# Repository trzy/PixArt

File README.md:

# PixArt PAJ7025R2 6dof Tracking Demo with Arduino and Windows

*Copyright 2017-2019 Bart Trzynadlowski*

## Overview

The PixArt PAJ7025R2 is an infrared camera with integrated DSP capable of tracking multiple IR light sources at high frame rates. Its predecessor was used in Nintendo's Wii Remote controller. [Johnny Chung Lee](http://johnnylee.net/projects/wii/), [Oliver Kreylos](https://web.cs.ucdavis.edu/~okreylos/ResDev/Wiimote/index.html  ), and [Franklin Ta](https://franklinta.com/2014/09/30/6dof-positional-tracking-with-the-wiimote/) have each demonstrated how to use the Wii sensor
for fun 6dof tracking applications.

In 2017, I got the idea to use the sensor in conjunction with Microsoft HoloLens for 6dof tracking of a tennis racket. I only got as far as
fabricating a test PCB to mount the chip before I shelved it. Two years later, feeling bad that I had never done anything with the boards, I built a PC
interface using Arduino and wrote a simple program to track and render an IR target in real-time.

This repository includes:

- Arduino code for the [Adafruit Feather nRF52 Bluefruit LE (nRF52832) board](https://www.adafruit.com/product/3406)
- Windows code for pose estimation (OpenCV 4.0.1) and visualization (SDL2 and OpenGL)
- PCB schematics and Gerbers files sent to [PCB Unlimited](https://pcbunlimited.com/) for fabrication
- Photographs of the assembled hardware, including a simple 9V battery-powered target with four 875 nm IR LEDs ([TSHA4400](https://www.vishay.com/ir-emitting-diodes/list/product-81017/)) by Vishay Semiconductors.

The Arduino reads out the detection report for each frame and sends it to the Windows program, which runs OpenCV's perspective-n-point (PnP) solver to estimate the 6dof pose of a target with known dimensions.

A PAJ7025R3 part with a wider field of view exists. To my knowledge, it is the exact same IC but with a different lens, meaning a simple modification of the camera
intrinsics in `code/win32/src/include/pixart/camera_parameters.hpp` would be the only change needed to support it.

## Build Instructions

### Arduino

The Arduino code is located in `code/arduino/pa_driver`. The other Arduino programs are simple tests. [Follow the instructions from Adafruit](https://learn.adafruit.com/bluefruit-nrf52-feather-learning-guide/arduino-bsp-setup) for
installing the BSP and loading the code onto the board.

Connections between the PixArt PCB and the Arduino board are listed in the table below.

| PixArt PCB | nRF52832 |
| ---------- | -------- |
| J1 (VDDMA) | +3.3v (recommend pin nearest GND) |
| J2 (G9/CSB) | A0 |
| J3 (G10/SCK) | SCK |
| J4 (G11/MISO) | MISO |
| J5 (G12/MOSI) | MOSI |
| J6 (GND) | GND |

### Windows

The Windows program located in `code/win32` depends on:

- [Boost](https://www.boost.org/) 1.69.0
- [OpenCV](https://opencv.org) 4.0.1
- [SDL2](https://libsdl.org)

Newer versions of Boost and OpenCV are untested but should work.

A Makefile for GCC on Windows is included. Edit the *Search Paths* section as needed. I used [MSYS2](https://msys2.org) to install GCC and SDL2 via pacman. OpenCV and Boost were installed manually.
Once ready simply run Make from the `code/win32` directory in an MSYS2 shell or Windows Command Prompt:

```
make
```

Visual Studio users will unfortunately have to manually create a project. I will happily accept a pull request for Visual Studio or CMake.

## Usage

In `code/win32` run:

```
bin/object_visualizer.exe
```

Two windows will appear (probably atop each other), one showing the raw objects detected by the sensor and the other showing a visualization of
a ping pong paddle in 3D. This assumes that an identical IR target to mine is being used. The target is defined in `code/win32/src/apps/object_visualizer/perspective_window.cpp`.
If there is an error opening the COM port, make sure the USB drivers were installed. These should come bundled with the Arduino IDE but can also
be obtained directly ([instructions here](https://learn.adafruit.com/bluefruit-nrf52-feather-learning-guide/arduino-board-setup)).

To test without any hardware, some recorded data is provided in `code/win32/recordings`. For example, try:

```
bin/object_visualizer.exe --replay-from=recordings/paddle0.bin
```

To learn about command line options, run:

```
bin/object_visualizer.exe --help
```

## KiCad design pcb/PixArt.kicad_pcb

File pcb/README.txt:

Cutout
------

Cutout was created using an NPTH pad, with hole and pad dimensions being identical.  Then, the following procedure
was used to copy this to the Edge.Cuts layer (while also retaining it in "All copper layers", or wherever the hole appears
by default).

https://stackoverflow.com/questions/43949808/create-a-footprint-for-mounting-through-the-board-cut-in-kicad

  (pad "" np_thru_hole oval (at 0 0) (size 12.5 1.2) (drill oval 12.5 1.2) (layers *.Cu Eco1.User))
  (pad "" np_thru_hole oval (at 0 0) (size 12.5 1.2) (drill oval 12.5 1.2) (layers *.Cu Edge.Cuts))

Mounting Holes
--------------

Two mounting holes were created as NPTH pads with diameter 0.9 mm.

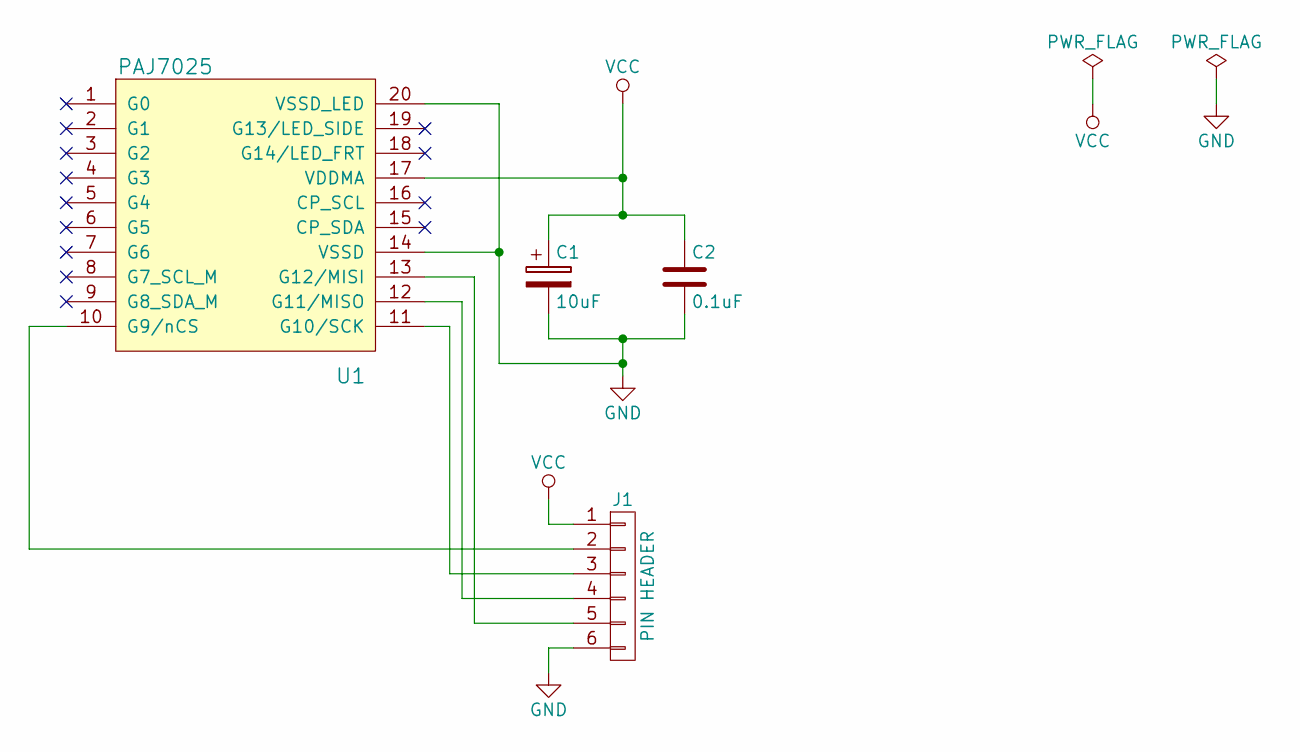
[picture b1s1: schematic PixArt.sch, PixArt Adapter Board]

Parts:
C1: 10uF; CP_Radial_D10.0mm_P2.50mm
C2: 0.1uF; C_Disc_D3.8mm_W2.6mm_P2.50mm
J1: PIN HEADER; Molex_KK-6410-06_06x2.54mm_Straight
U1: PAJ7025

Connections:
GND: C1.2, C2.2, J1.6, U1.14 (VSSD), U1.20 (VSSD_LED)
unnamed: J1.2, U1.10 (G9/nCS)
unnamed: J1.3, U1.11 (G10/SCK)
unnamed: J1.4, U1.12 (G11/MISO)
unnamed: J1.5, U1.13 (G12/MISI)
VCC: C1.1, C2.1, J1.1, U1.17 (VDDMA)

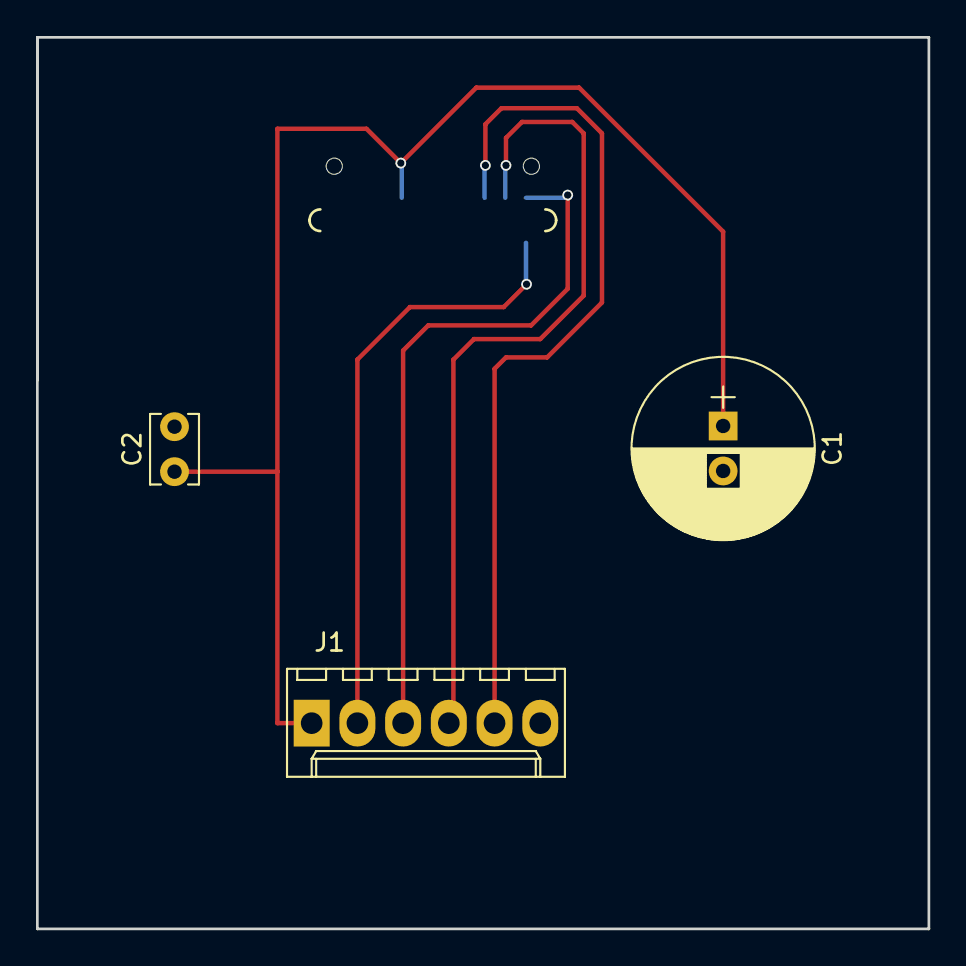
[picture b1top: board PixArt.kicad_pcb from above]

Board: 2 copper layers, 49.5 x 49.5 mm, 4 parts (0 on the bottom side), 6 nets.

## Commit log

2021-09-11 Report position every second
2021-09-11 Added IR LED datasheets and Feather board manuals
2021-09-11 Added TSHA4400 (875nm IR LED) datasheet. This LED confirmed to work with PixArt sensor.
2021-09-11 Whitespace
2021-09-11 Arduino pa_driver app can respond to peek and poke requests
2021-09-11 Added wait_for_packets(), which blocks until n expected packets are received
2021-09-11 Cooperative task object for periodic tasks
2021-09-11 Packet id member type is now PacketID
2021-09-11 USB ping test
2021-09-11 New packet_reader class for cooperatively reading packets from serial port stream
2021-09-11 Moved cooperative_task into util namespace, commented namespace closing brackets, whitespace fixes
2021-09-11 PixArt driver: set up and read object data, verify by printing to serial console
2021-09-11 Reorganized source code and added a Windows-based serial test program
2021-09-11 Fix infinite loop in cooperative_task
2021-09-11 Unity doesn't work reliably; removing it.
2021-09-11 Non-functional Unity app
2021-09-11 Oops :(
2021-09-11 Reorg of code
2021-09-11 Added .gitignore
2021-09-11 Scripting run-time set to .NET 4.x to fix SerialPort.BytesToRead crash
2021-09-11 Read and dump sensor settings
2021-09-11 Added pa_driver_test.cpp (prints product ID), removed other test programs. Fixed Makefile to allow LDFLAGS overrides at the app level.
2021-09-11 Added comment
2021-09-11 Fixed a really tricky bug that was causing corruption (and could have caused crashes) at higher baud rates
2021-09-11 Print frame timing and object 0 coordinate
2021-09-11 Request and receive full object report packets
2021-09-11 Comment
2021-09-11 Object visualizer app. For now, prints sensor info, ASCII rendering, and object data.
2021-09-11 Reorged files. Command line options for sensor printout, ASCII object dump, and 2D viewer.
2021-09-11 Bumped up baud rate to 115200
2021-09-11 Moved PA_object into its own module so it can be shared with non-Arduino client code
2021-09-11 peek_response_packet includes bank and address
2021-09-11 Print default option values in command line help
2021-09-11 Add OpenCV camer calibration libraries for solvePnP
2021-09-11 Added command line options for serial port and baud rate
2021-09-11 Added object write method and changed an error message
2021-09-11 Fixed uninitialized variable error and simplified logic
2021-09-11 Fixed for clang's strict type checker
2021-09-11 Reformatted serial_port class and made it throw instead of printing errors
2021-09-11 Added size() to packet_header
2021-09-11 SDL2-based visualization of objects in sensor frame
2021-09-11 Forgot to add required build file
2021-09-11 Main loop can handle arbitrary number of windows
2021-09-11 PixArt camera parameters
2021-09-11 Factored rendering code out to its own module
2021-09-11 set_camera() rotation parameter now takes a euler3 instead of vector3
2021-09-11 serial_replay_device: additional error checking
2021-09-11 window_3d: set GL context
2021-09-11 Refactored window classes, turning them into base classes and moving object view logic into a derived class
2021-09-11 Serial port recording and playback via serial_replay_device class
2021-09-11 Created i_serial_device interface to hide serial port implementation
2021-09-11 Spinning cube
2021-09-11 Scoped, node-based rendering of boxes to create model of target circuit board
2021-09-11 Added glu32 to OpenGL libs
2021-09-11 Added i_window and windows_2d to wrap SDL windows
2021-09-11 window_3d: OpenGL-based window. Using it for 2D object view for now to verify basic functionality.
2021-09-11 Windows can be closed independently
2021-09-11 Sample serial captures
2021-09-11 Improved camera parameters
2021-09-11 Transform node from OpenCV rotation matrix and translation vector. Near clipping plane 0.1 -> 0.01.
2021-09-11 Using solvePnPRansac() for perspective view. Rotation is mostly wrong.
2021-09-11 pnp_test.inc
2021-09-11 i_window::init() method
2021-09-11 IR target board rendering uses (close to) physical scale
2021-09-11 Added temporal consistency (attempt to match points to prior frame)
2021-09-11 No need to preallocate matrices. Meaningful object position chosen.
2021-09-11 Refactored LED board drawing code into own function
2021-09-11 Sensor settings object and changed print_sensor_settings() -> read_sensor_settings()
2021-09-11 No longer constexpr
2021-09-11 First crude attempt at canonicalization of image point order for stable solutions
2021-09-11 Position and rotation (Rodrigues) vectors are 3x1
2021-09-11 Comments
2021-09-11 Allow different image resolutions to be used to compute focal length
2021-09-11 pnp_test: Example of how to use cv::solvePnP()
2021-09-11 Recording with IR target board attached to ping pong paddle
2021-09-11 Draw paddle
2021-09-11 Added a paper reference on 2D-3D point correspondence
2021-09-11 PnP solver and whether to use RANSAC are selectable on command line
2021-09-11 Refactored object_window: hid implementation
2021-09-11 Refactored perspective_window: hide implementation entirely and use a factory method
2021-09-11 Commented out debug printouts
2021-09-11 C++ method pointer example
2021-09-11 Configuration for perspective_window put in its namespace
2021-09-11 Photo of hardware
2021-09-11 object_window and perspective_window into own files
2021-09-11 Configuration for object_window put in its namespace
2021-09-11 Cleanup perspective_window
2021-09-11 Sensor resolution setting
2021-09-11 Draw LED board on paddle
2021-09-14 Added README.md, new photos and a demo GIF, and added Arduino board connetions to pa_driver
2021-09-14 Slight Makefile change to fix build in MSYS2
